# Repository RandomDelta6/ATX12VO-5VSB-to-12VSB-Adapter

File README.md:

# Introduction

This is a ATX12VO Standard compatible +5VSB to +12VSB Converter Circuit. It is based around the FP6296 chip which is a current mode boost DC-DC converter. This board enables older power supplies which output 12V, 5V, 3V Rails to be compatible with the new ATX12VO Standard. This board features a universal design and is compatible with Power Supplies from any lineup of any manufacturer. Please refer to your PSU output pinout and ATX12VO Connector pinout to route the connecting wires for the connector cable properly. This board only converts the +5VSB rail to +12VSB rail as needed in ATX12VO standard.

This board is expected to go inline in the PSU to ATX12VO motherboard connector cable and be sleeved, which would make it look similar to the above cable.

This board features an extremely small form factor of 16.8mm x 17.3mm so that it can be easily incorporated inline in a sleeved ATX12VO Motherboard Connector cable. The compact size of the board and dense arrangement of components make it highly resilient to bending or breakage while attempting to cable manage or route ATX12VO Motherboard Connector cable in a tight PC case. The small form factor also ensures the flexibility of the cable is not compromised when installed inline. The larger the inline circuit board, the lesser the flexibility. Reduced flexibility of cable can result in difficulty in cable management or unsatisfactory results in cable management.

# Schematic

# PCB

PCB Front View

PCB Back View

# Usage

Proceed to place the diode and inductor on the back, these are held in place via the adhesive. Then place the front smd components and reflow solder the entire assembly. Thread in the cables from the back and solder onto the front side, ensure enough solder flows to make a solid connection through the plated through hole and solder flows across to the exposed contact on the back side. Please note that +12V and GND terminals are pretty close, ensure the terminals are not bridged during soldering.

It is to be noted that +5VSB commences at the PSU Connector end and terminates at this board while +12VSB originates at this board and continues to the ATX12VO Motherboard Connector. +12V and GND wires are to run across the cable from the PSU connector end to the motherboard connector end and the +12V and GND connections for this board may use wires spliced in with the +12V and GND wires running across the cable or have dedicated wires run through the PSU connector end to the +12V and GND terminals of this board. The inline circuit assembly maybe encapsulated with a heatshrink for better isolation. It can then be bundled together with the other wires running across the cable and be sleeved together. 

# Notes

This board prioritises small form factor above all else and as such will have a performance penalty as opposed to the reference layout which uses a two layer design with single sided component layout spread out over a much larger area with global ground net on bottom layer. 

Mounting the magnetic component (Inductor) directly on the otherside of the controller introduces significant noise and coupling. As such a 4 layer PCB is required for isolation which is achieved by flooding ground in the middle two copper layers as well as underneath the inductor on the bottom layer. This should provide significant shielding to signal lines and the throughly stitched ground planes should ensure low impedance across ground net. This minimises the magnetic effect but does not completely isolate it, as such a nominal coil whine is to be expected. This design uses all smd components to reduce noise bleed and isolate switching noise to ensure minimal noise characteristics on output line.

The reference design might be cheaper as it utilises 2 layers as opposed to 4 layers in this design, but the cost difference should be negligible on a per unit basis when panelized due to the smaller board footprint in this design which would net more boards from a similar sized panel. Thorough use of vias in this design is necessary for proper signal integrity even though it might increase expense. Thick signal traces are used wherever necessary to minimise the inductive effect of the tracks for high frequency signals. Ceramic Capacitors with low ESR must be used. MLCC X5R and X7R Series are recommended.

Although I am pretty confident the board should work, you might still wish to have the board verified by a professional. I am not particularly confident about the values of C4 and C10.

Couldn't find a proper model for Inductor L1 and Diodes D1 and D2, so they are missing on the PCB views.

This project was made with Kicad 7.0 .
Generate gerbers as per specification from the fab of your choice.

# Disclaimer
This board has not been printed and tested physically to verify functionality. I do not assume any liability for the materials, information and opinions provided on, or available through, this project. I disclaim any liability for injury, death or damages resulting from the use thereof. Modify or work on it at your own risk.

# Licensing
All PCB design files and hardware are released under the [Creative Commons Attribution Share Alike 4.0 license](https://choosealicense.com/licenses/cc-by-sa-4.0/). 

Commercial Usage strictly disallowed.

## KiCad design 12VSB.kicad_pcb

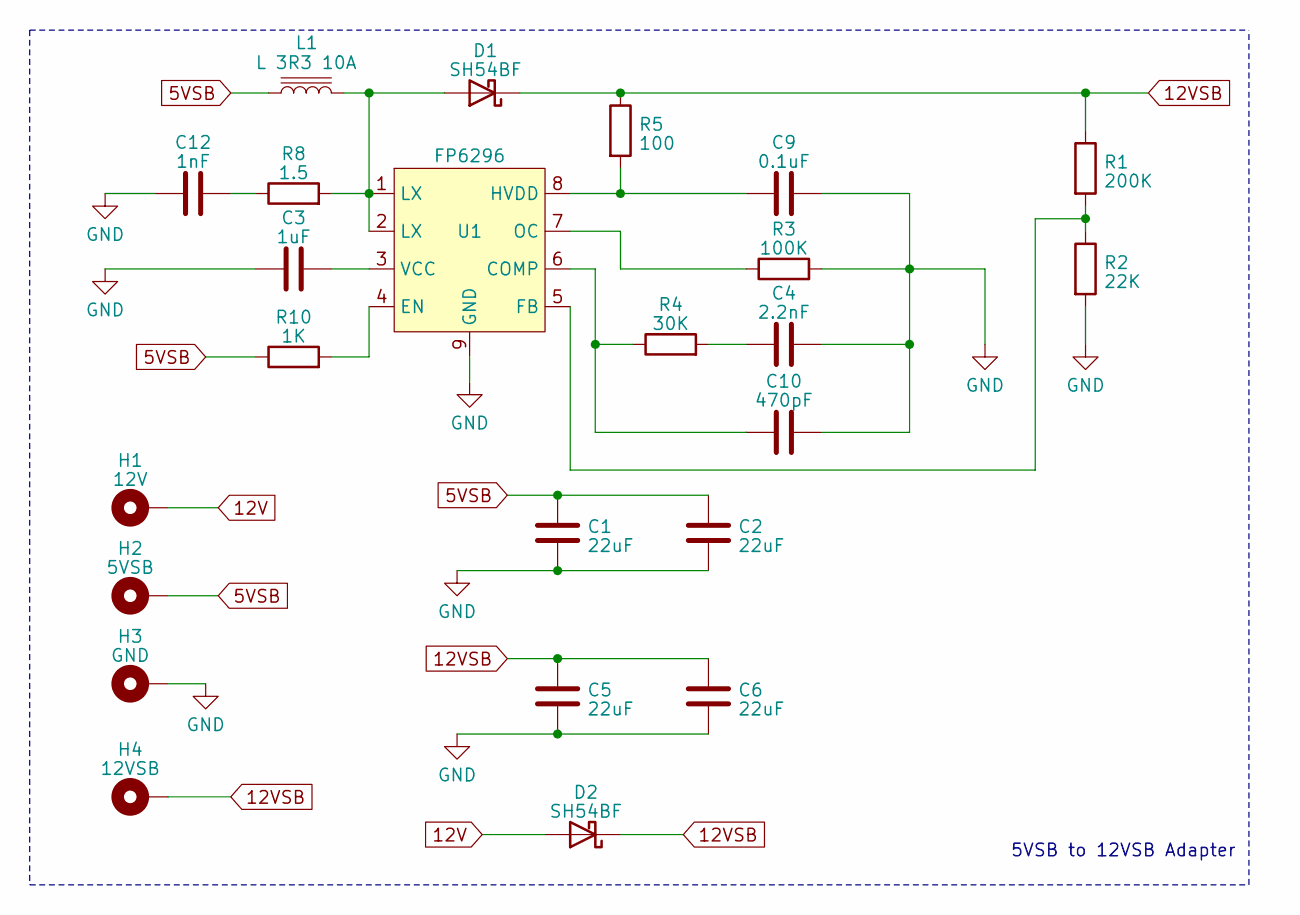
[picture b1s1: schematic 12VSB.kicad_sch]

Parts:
C1, C2, C5, C6: 22uF; C_0805_2012Metric
C3: 1uF; C_0603_1608Metric
C4: 2.2nF; C_0402_1005Metric
C9: 0.1uF; C_0603_1608Metric
C10: 470pF; C_0402_1005Metric
C12: 1nF; C_0603_1608Metric
D1, D2: SH54BF; diode
H1: 12V; MountingHole_2.2mm_M2_DIN965_Pad
H2: 5VSB; MountingHole_2.2mm_M2_DIN965_Pad
H3: GND; MountingHole_2.2mm_M2_DIN965_Pad
H4: 12VSB; MountingHole_2.2mm_M2_DIN965_Pad
L1: L 3R3 10A; INDM125125X800N
R1: 200K; R_0402_1005Metric
R2: 22K; R_0402_1005Metric
R3: 100K; R_0402_1005Metric
R4: 30K; R_0402_1005Metric
R5: 100; R_0603_1608Metric
R8: 1.5; R_0603_1608Metric
R10: 1K; R_0603_1608Metric
U1: FP6296

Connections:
5VSB: C1.1, C2.1, H2.1, L1.1, R10.1
12V: D2.2 (A), H1.1
12VSB: C5.1, C6.1, D1.1 (K), D2.1 (K), H4.1, R1.1, R5.1
GND: C1.2, C2.2, C3.1, C4.2, C5.2, C6.2, C9.2, C10.2, C12.2, H3.1, R2.2, R3.2, U1.9 (GND)
unnamed: C4.1, R4.2
unnamed: C12.1, R8.1
unnamed: D1.2 (A), L1.2, R8.2, U1.1 (LX), U1.2 (LX)
unnamed: C10.1, R4.1, U1.6 (COMP)
unnamed: R10.2, U1.4 (EN)
unnamed: R1.2, R2.1, U1.5 (FB)
unnamed: C9.1, R5.2, U1.8 (HVDD)
unnamed: R3.1, U1.7 (OC)
unnamed: C3.2, U1.3 (VCC)

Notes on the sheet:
5VSB to 12VSB Adapter

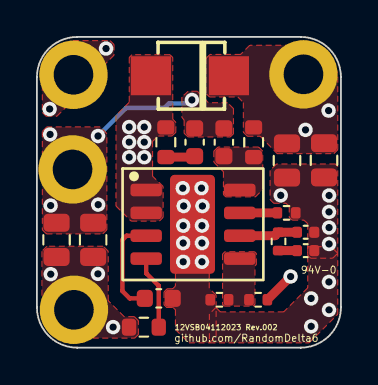
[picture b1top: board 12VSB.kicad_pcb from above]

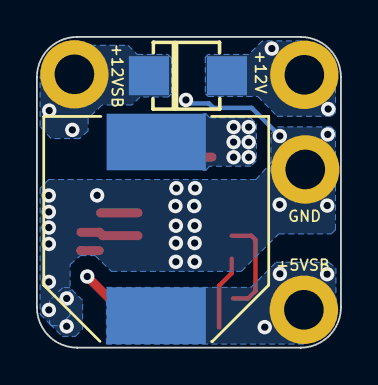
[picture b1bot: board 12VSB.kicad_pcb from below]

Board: 4 copper layers, 16.9 x 17.3 mm, 24 parts (2 on the bottom side), 13 nets.

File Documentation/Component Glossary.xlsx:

List of Materials
Sl. No. | Notation | Type | Description | Value | Particulars
1 | U1 | Controller |  |  | FP6296
2 | C1 | Capacitor | SMD 0805_2012 | 22uF
3 | C2 | Capacitor | SMD 0805_2012 | 22uF
4 | C3 | Capacitor | SMD 0603_1608 | 1uF
5 | C4 | Capacitor | SMD 0402_1005 | 2.2nF
6 | C5 | Capacitor | SMD 0805_2012 | 22uF
7 | C6 | Capacitor | SMD 0805_2012 | 22uF
8 | C9 | Capacitor | SMD 0603_1608 | 0.1uF
9 | C10 | Capacitor | SMD 0402_1005 | 470pF
10 | C12 | Capacitor | SMD 0603_1608 | 1nF
11 | D1 | Diode |  |  | SH54BF
12 | D2 | Diode |  |  | SH54BF
13 | L1 | Inductor | Radial-cylinderical | 3.3uH 10A | Shielded Drum Core 3R3
14 | R1 | Resistor | SMD 0402_1005 | 200KΩ | EIA 30D
15 | R2 | Resistor | SMD 0402_1005 | 22KΩ | EIA 223
16 | R3 | Resistor | SMD 0402_1005 | 100KΩ | EIA 01D
17 | R4 | Resistor | SMD 0402_1005 | 30KΩ | EIA 303
18 | R5 | Resistor | SMD 0603_1608 | 100Ω | EIA 101
19 | R8 | Resistor | SMD 0603_1608 | 1.5Ω | EIA 1R5
20 | R10 | Resistor | SMD 0603_1608 | 1KΩ | EIA 102

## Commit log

2023-04-07 initial pcb dump
2023-04-07 updated pcb layout
2023-04-09 Corrected Schema and updated PCB Layout
2023-04-09 initial pcb trace layout
2023-04-10 updated pcb track layout
2023-04-10 Updated PCB Layout and Documentation
2023-04-10 fixed diode footprint
2023-04-10 refined pcb tracks
2023-04-11 refined schematic and updated pcb layout
2023-04-11 corrected schematic
2023-04-11 Refined Silkscreens and added Documentation
2023-04-14 Updated schematic
2023-06-30 updated adhesive layers
